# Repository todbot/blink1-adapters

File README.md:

blink(1) adapters
=================

Little hardware add-ons to blink(1) USB RGB LED to allow more LEDs to be used.

* https://oshpark.com/projects/2awZS2hw

Also see:

* https://blog.thingm.com/2017/01/adding-neopixels-ws2812-leds-to-blink1/
* https://blog.thingm.com/2014/09/blink16-prototype-is-woody-and-awesome/

* https://blink1.thingm.com/

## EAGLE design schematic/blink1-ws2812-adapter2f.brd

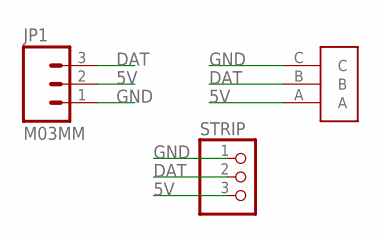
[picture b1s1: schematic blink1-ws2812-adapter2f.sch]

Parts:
JP1: M03MM; 1X03-1.5MM
STRIP: PINHD-1X3; 1X03
U$1: LED_STRIP_3P; LEDSTRIP-3P

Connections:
5V: JP1.2, STRIP.3, U$1.A
DAT: JP1.3, STRIP.2, U$1.B
GND: JP1.1, STRIP.1, U$1.C

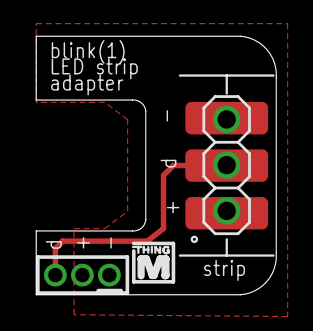
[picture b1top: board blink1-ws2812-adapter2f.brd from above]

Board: 2 copper layers, 13.3 x 14.4 mm, 3 parts (0 on the bottom side), 3 nets.
